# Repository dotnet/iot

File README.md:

# .NET IoT Libraries

.NET can be used to build applications for [IoT](https://en.wikipedia.org/wiki/Internet_of_things) devices and scenarios. IoT applications typically interact with sensors, displays and input devices that require the use of [GPIO pins](https://en.wikipedia.org/wiki/General-purpose_input/output), serial ports or similar hardware.

> [!IMPORTANT]
> This is the GitHub repo for the libraries. You might want to start with our [official documentation](https://docs.microsoft.com/dotnet/iot/).

This repository contains the [System.Device.Gpio](https://www.nuget.org/packages/System.Device.Gpio) library and implementations for various boards like [Raspberry Pi](https://www.raspberrypi.org/) and [Hummingboard](https://www.solid-run.com/nxp-family/hummingboard/).

The repository also contains [Iot.Device.Bindings](https://www.nuget.org/packages/Iot.Device.Bindings), a growing set of community-maintained [device bindings](src/devices/README.md) for IoT components.

The libraries in this repository are community-maintained and do not have a formal support commitment. Existing versions are not serviced. Fixes may be included in a future minor or major release.

> [!NOTE]
> This repository is still in experimental stage and all APIs are subject to changes.

## Hardware requirements

While most of the bindings and examples in this project require and are designed to support specific hardware (such as [LCD displays](src/devices/CharacterLcd), [temperature sensors](src/devices/Dhtxx), [single-board computers](src/devices/Board/RaspberryPiBoard.cs), [microcontrollers](src/devices/Arduino), etc.), the library itself tries to be as hardware-independent as possible. Some bindings are even written to showcase the use of IOT interfaces with hardware that is already present in normal desktop computers (such as [keyboards](src/devices/Board/KeyboardGpioDriver.cs) or [CPU temperature sensors](src/devices/HardwareMonitor)). So to get started, you do not need expensive hardware. Or you can start out with cheap stuff, such as an Arduino Uno.

## .NET Versions

Both libraries in this repository are cross-targeting .NET Standard 2.0, .NET Core 3.1, and .NET 6.0. They can be used from any project targeting .NET Core 2.0 or higher, and also from .NET Framework or mono. If you are looking at a Micro Controller Unit (MCU) support, check [.NET nanoFramework](https://github.com/nanoframework/).

The sample projects target the latest stable .NET Version. This applies to the sample projects with each device as well as the example projects on the `/samples` directory.

## How to Install

From Visual Studio, you can just add a nuget by searching for `System.Device.Gpio` and `Iot.Device.Bindings`.

### Nightly Builds

You can also install the latest nightly builds of the .NET `System.Device.Gpio`, `Iot.Device.Bindings`, and `Iot.Device.Bindings.SkiaSharpAdapter` NuGet packages. These are automatically published from the latest commits to the main branch.

#### Azure DevOps Feed (No Authentication Required)

Add the nightly feed to your project:

```shell
# Add the Azure DevOps nightly feed (no authentication required)
dotnet nuget add source --name dotnet-iot-nightly "https://pkgs.dev.azure.com/dotnet/IoT/_packaging/nightly_iot_builds/nuget/v3/index.json"

# Install packages
dotnet add package System.Device.Gpio --source dotnet-iot-nightly --prerelease
dotnet add package Iot.Device.Bindings --source dotnet-iot-nightly --prerelease
dotnet add package Iot.Device.Bindings.SkiaSharpAdapter --source dotnet-iot-nightly --prerelease
```

Or add to your `NuGet.config`:

```xml
<packageSources>
  <add key="dotnet-iot-nightly" value="https://pkgs.dev.azure.com/dotnet/IoT/_packaging/nightly_iot_builds/nuget/v3/index.json" />
</packageSources>
```

### Official Build Status

## Contributing

For information on how to build this repository and to add new device bindings, please head out to [Contributing](Documentation/CONTRIBUTING.md).

Please contribute. We are primarily interested in the following:

* Improving quality and capability of the drivers for supported boards.
* Implementations for additional boards.
* [.NET device bindings](src/devices) for a wide variety of sensors, chips, displays and other components.
* Request a device binding or protocol that you need for your project ([file an issue](https://github.com/dotnet/iot/issues)).
* Links to blog posts or tweets that showcase .NET Core being used for great IoT scenarios ([file an issue](https://github.com/dotnet/iot/issues)).

## Getting Started

After installing, please see the following areas to learn more:

* [Official Documentation](https://docs.microsoft.com/dotnet/iot/) - Concepts, quickstarts, tutorials, and API reference documentation.
* [API Documentation](https://docs.microsoft.com/dotnet/api/?view=iot-dotnet-1.5) - Direct link to API reference documentation for all public interfaces. Be sure to choose the library version you are using.
* [Microsoft Learn interactive learning module](https://docs.microsoft.com/learn/modules/create-iot-device-dotnet/)
* [Let's Learn .NET: IoT livestream (September 2021)](https://www.youtube.com/watch?v=sKaSBh1M4M4)
* [.NET IoT 101 (Jan 2020)](https://channel9.msdn.com/Series/IoT-101) - An introduction series on how to create .NET IoT applications with a Raspberry Pi.
* [Hardware Documentation](Documentation/README.md) - Resources related to electronics, devices, vendors, software and other IoT topics.
* [Samples](samples/README.md) - Step-by-step instructions on building your first app.
* [Roadmap](Documentation/roadmap.md) - Areas planned or currently being worked on.

All bindings (src/devices) contains a `samples` folder where you will find examples on how to use each of the devices, sensor, displays and other components.

**Important**: Please make sure you are using tag that correspond to your package version to browse and reuse the samples' code.

Once you have selected the right branch, you can browse the repository. The main branch contains code that is always the latest and may not been yet released to a package. So if you are using the 1.2 package, please select 1.2 tag before browsing the source code.

### Tutorials

* [Web service using SenseHat by Dawid Borycki (Aug 2019)](https://msdn.microsoft.com/magazine/mt833493)

## Community

This project has adopted the code of conduct defined by the [Contributor Covenant](https://contributor-covenant.org/)
to clarify expected behavior in our community. For more information, see the [.NET Foundation Code of Conduct](https://dotnetfoundation.org/code-of-conduct).

## License

.NET (including the iot repo) is licensed under the [MIT license](LICENSE).

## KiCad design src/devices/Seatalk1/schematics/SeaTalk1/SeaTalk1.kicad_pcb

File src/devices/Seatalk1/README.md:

# Seatalk 1 Interface

## Summary

Seatalk, also called Seatalk1, is a bus protocol used by the marine equipment company Raymarine. It is used as a protocol to connect various devices on a boat, such as depth sounders, anemometers (wind sensors), autopilots and displays. The protocol is the successor of NMEA-0183, providing the main benefit of being able to connect various devices to a single bus, without the need of complex star networks and bridges as it was required for NMEA-0183.

Data transfer uses a slow transmission rate of 4800 Baud, but this makes the bus quite stable with respect to interference. Collisions do occur, but as most messages are repeated at least every second, lost messages are typically negligible.

Seatalk has been superseeded by NMEA-2000, but some older devices are still only available with NMEA-0183 or Seatalk. Interfaces to convert between the various standards are available from different vendors.

> Note: Seatalk is often called Seatalk1, to distinguish it from SeatalkNG (Seatalk "Next Generation"). The latter is a branded version of NMEA-2000. NMEA-2000 and SeatalkNG are binary and electrically compatible, but use different plugs and sockets.

## Binding Notes

The binding provides the message definitions for various Seatalk messages. Using the proper interface (see below), it supports receiving and transmitting Seatalk messages. The binding is primarily intended to control older autopilots, such as the Raymarine ST1000+ and ST2000+. Not all known sentence types are supported, but the binding allows registering of further messages.

A bi-directional Seatalk to NMEA-0183 message converter is also included.

Example: (for full source, see example directory)

```csharp
_seatalk = new SeatalkInterface("/dev/ttyAMA2"); // Or some other serial interface
_seatalk.MessageReceived += ParserOnNewMessageDecoded;
_seatalk.StartDecode();
var ctrl = _seatalk.GetAutopilotRemoteController();

if (ctrl.SetStatus(AutopilotStatus.Auto, ref directionConfirmation))
{
    Console.WriteLine("Autopilot set to AUTO mode");
}
else
{
    Console.WriteLine("Setting AUTO mode FAILED!");
}

await Task.Delay(500);

NavigationToWaypoint wp = new NavigationToWaypoint()
{
    BearingToDestination = Angle.FromDegrees(10),
    CrossTrackError = Length.FromNauticalMiles(-0.11),
    DistanceToDestination = Length.FromNauticalMiles(51.3),
};

_seatalk.SendMessage(wp);

private void ParserOnNewMessageDecoded(SeatalkMessage obj)
{
    if (obj is Keystroke keystroke)
    {
        Console.WriteLine();
        Console.WriteLine($"Pressed key(s): {keystroke}");
    }
}

```

## Physical interface

The physical bus uses a kind of UART protocol, but since it uses a single wire both for sending and receiving, additional electronics are required to connect the bus to an UART (RS-232) interface. Protocol converters are available on the market. The following scheme shows a schematic that allows connecting a Seatalk network to a Raspberry Pi. The seatalk cable is connected to J3. The grey wire from the bus goes to GND, the yellow wire is the data wire and the red wire is +12V. In this schematic, connecting the 12V wire is optional as long as there's at least one other device on the bus that provides the necessary pull-up. The wiring shows a connection to TXD2/RXD2 (ttyAMA2 on linux), as this interface is easier to configure than the default one on GPIO14/15, as long as it's enabled in `boot/config.txt` with `dtoverlay=uart2`.

When connecting to a default RS-232 interface (e.g. using an USB-to-RS-232 converter), the inverting stages Q2 on RXD and Q5 on TXD should be skipped. Powering the entire wiring via 12V should work with some minor adjustments, such as changing R9 to 470Ω to avoid destroying D1.

## References

Many tanks to Thomas Knauf for his extensive Seatalk protocol analysis. See [here](http://www.thomasknauf.de/seatalk.htm)

OpenCPN Seatalk Support [here](https://opencpn.org/wiki/dokuwiki/doku.php?id=opencpn:supplementary_software:seatalk).

The OpenCPN plugin "Raymarine Autopilot" can send the required keypress sentences for remote-controlling an autopilot, but needs an NMEA-0183 to Seatalk1 bridge, which can be built using this binding.

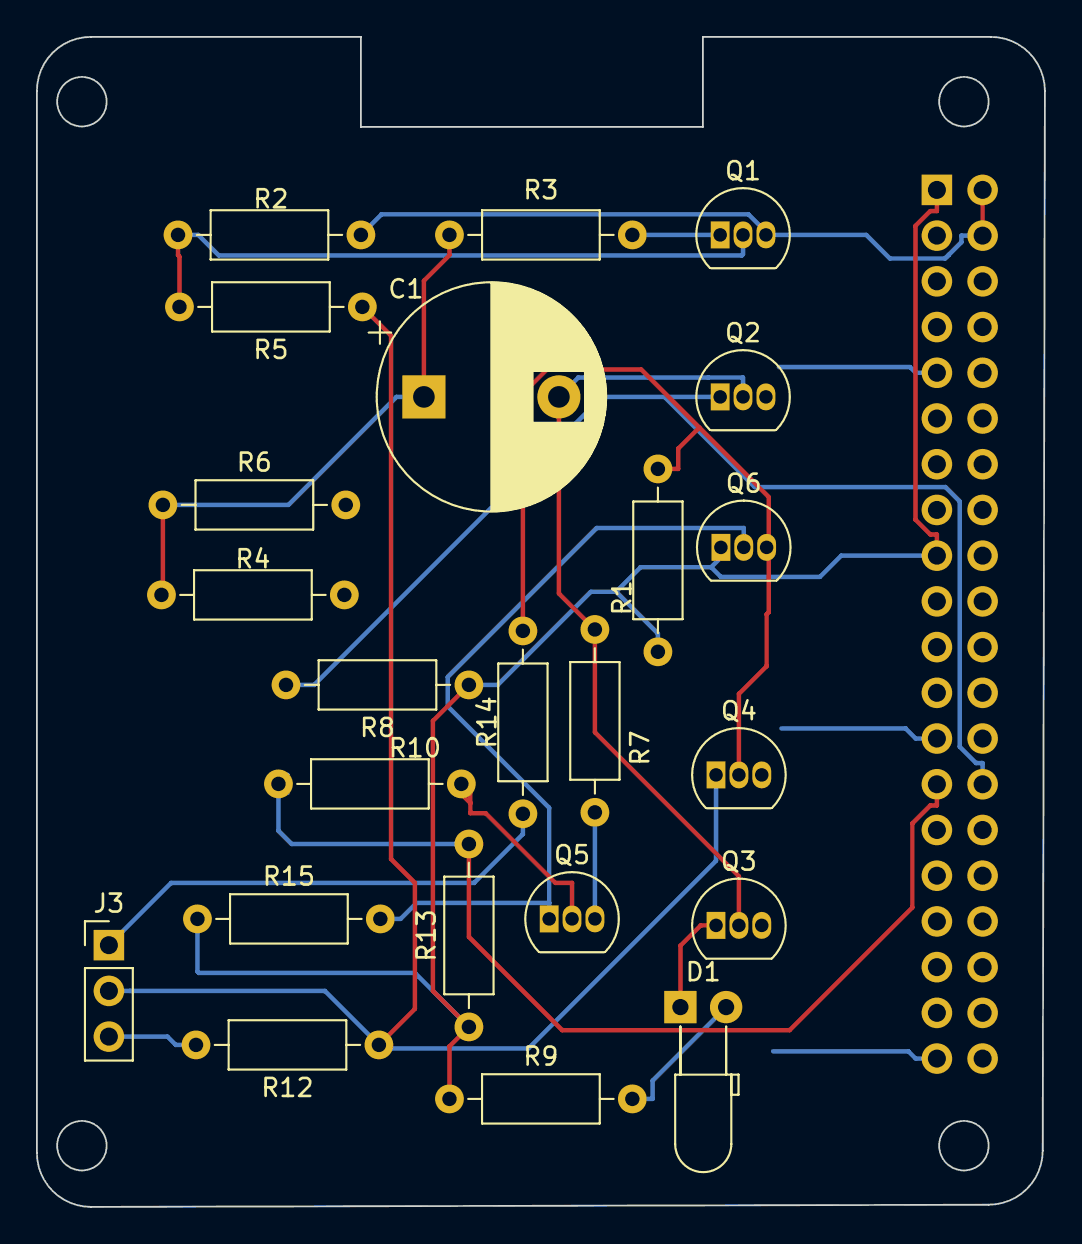
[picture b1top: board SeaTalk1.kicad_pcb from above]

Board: 2 copper layers, 56.0 x 65.0 mm, 24 parts (1 on the bottom side), 16 nets.

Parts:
C1: 150u; CP_Radial_D12.5mm_P7.50mm
D1: blue; LED_D3.0mm_Horizontal_O3.81mm_Z6.0mm
J1: Raspberry_Pi_2_3; PinSocket_2x20_P2.54mm_Vertical
J3: Conn_01x03_Pin; PinHeader_1x03_P2.54mm_Vertical
Q1: BC557; TO-92_Inline
Q2, Q3, Q4, Q5, Q6: BC547; TO-92_Inline
R1, R7: 22k; R_Axial_DIN0207_L6.3mm_D2.5mm_P10.16mm_Horizontal
R2, R3, R8, R14: 2.2k; R_Axial_DIN0207_L6.3mm_D2.5mm_P10.16mm_Horizontal
R4, R5, R6: 4.7k; R_Axial_DIN0207_L6.3mm_D2.5mm_P10.16mm_Horizontal
R9: 100; R_Axial_DIN0207_L6.3mm_D2.5mm_P10.16mm_Horizontal
R10: 1.5k; R_Axial_DIN0207_L6.3mm_D2.5mm_P10.16mm_Horizontal
R12, R13, R15: 10k; R_Axial_DIN0207_L6.3mm_D2.5mm_P10.16mm_Horizontal

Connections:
GND: J1.6 (GND), J1.9 (GND), J1.14 (GND), J1.20 (GND), J1.25 (GND), J1.30 (GND), J1.34 (GND), J1.39 (GND), J3.1, Q2.3 (E), Q3.3 (E), Q4.3 (E), Q5.3 (E), R4.2, R6.2, R7.2, R14.2
unnamed: C1.1, R3.2, R4.1, R6.1
unnamed: D1.2 (A), R9.2
unnamed: D1.1 (K), Q3.1 (C)
unnamed: J1.28 (ID_SC/GPIO1), Q2.1 (C), R8.2
unnamed: J3.3, R12.2
unnamed: Q1.2 (B), R2.2, R5.2
unnamed: Q1.1 (C), R3.1
unnamed: C1.2, Q2.2 (B), Q3.2 (B), R7.1
unnamed: Q4.2 (B), Q6.3 (E), R1.2, R14.1
unnamed: Q5.2 (B), R10.2
unnamed: Q5.1 (C), Q6.2 (B), R15.2
SEATALK: J3.2, Q4.1 (C), R5.1, R12.1
TXD: J1.27 (ID_SD/GPIO0), R10.1, R13.2
VCC_3.3: J1.1 (3V3), J1.17 (3V3), Q6.1 (C), R1.1, R8.1, R9.1, R13.1, R15.1
VCC_5.0: J1.2 (5V), J1.4 (5V), Q1.3 (E), R2.1

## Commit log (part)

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2026-05-09 Looks better now, maybe?
2026-05-10 Bump Microsoft.DotNet.Helix.Sdk from 9.0.0-beta.26223.2 to 9.0.0-beta.26255.11 (#2523)
    ---
    updated-dependencies:
    - dependency-name: Microsoft.DotNet.Helix.Sdk
    dependency-version: 9.0.0-beta.26255.11
    dependency-type: direct:production
    update-type: version-update:semver-patch
2026-05-11 Designed new filter interface
2026-05-13 Bump Microsoft.DotNet.GenAPI from 9.0.0-beta.26255.11 to 9.0.0-beta.26261.1
    ---
    updated-dependencies:
    - dependency-name: Microsoft.DotNet.GenAPI
    dependency-version: 9.0.0-beta.26261.1
    dependency-type: direct:production
    update-type: version-update:semver-patch
2026-05-13 Bump Microsoft.Extensions.Logging from 10.0.7 to 10.0.8
    ---
    updated-dependencies:
    - dependency-name: Microsoft.Extensions.Logging
    dependency-version: 10.0.8
    dependency-type: direct:production
    update-type: version-update:semver-patch
2026-05-13 Bump System.Drawing.Common from 10.0.7 to 10.0.8
    ---
    updated-dependencies:
    - dependency-name: System.Drawing.Common
    dependency-version: 10.0.8
    dependency-type: direct:production
    update-type: version-update:semver-patch
2026-05-13 Bump Microsoft.Extensions.Logging.Abstractions from 10.0.7 to 10.0.8
    ---
    updated-dependencies:
    - dependency-name: Microsoft.Extensions.Logging.Abstractions
    dependency-version: 10.0.8
    dependency-type: direct:production
    update-type: version-update:semver-patch
2026-05-13 Bump System.IO.Ports from 10.0.7 to 10.0.8
    ---
    updated-dependencies:
    - dependency-name: System.IO.Ports
    dependency-version: 10.0.8
    dependency-type: direct:production
    update-type: version-update:semver-patch
2026-05-13 Bump System.Management from 10.0.7 to 10.0.8
    ---
    updated-dependencies:
    - dependency-name: System.Management
    dependency-version: 10.0.8
    dependency-type: direct:production
    update-type: version-update:semver-patch
2026-05-14 Bump System.IO.Pipelines from 10.0.7 to 10.0.8 (#2532)
    ---
    updated-dependencies:
    - dependency-name: System.IO.Pipelines
    dependency-version: 10.0.8
    dependency-type: direct:production
    update-type: version-update:semver-patch
2026-05-14 Bump Microsoft.Extensions.Logging from 10.0.7 to 10.0.8 (#2530)
    ---
    updated-dependencies:
    - dependency-name: Microsoft.Extensions.Logging
    dependency-version: 10.0.8
    dependency-type: direct:production
    update-type: version-update:semver-patch
2026-05-14 Bump Microsoft.DotNet.Arcade.Sdk from 9.0.0-beta.26255.11 to 9.0.0-beta.26261.1 (#2527)
    ---
    updated-dependencies:
    - dependency-name: Microsoft.DotNet.Arcade.Sdk
    dependency-version: 9.0.0-beta.26261.1
    dependency-type: direct:production
    update-type: version-update:semver-patch
2026-05-14 Bump Microsoft.DotNet.Helix.Sdk from 9.0.0-beta.26255.11 to 9.0.0-beta.26261.1
    ---
    updated-dependencies:
    - dependency-name: Microsoft.DotNet.Helix.Sdk
    dependency-version: 9.0.0-beta.26261.1
    dependency-type: direct:production
    update-type: version-update:semver-patch
2026-05-14 Bump System.IO.Ports from 10.0.7 to 10.0.8 (#2534)
    ---
    updated-dependencies:
    - dependency-name: System.IO.Ports
    dependency-version: 10.0.8
    dependency-type: direct:production
    update-type: version-update:semver-patch
2026-05-14 Fix SpiAdapter.Read buffer length mismatch for TransferFullDuplex
    Allocate writeBuffer at the same length as readBuffer (buffer.Length + 2)
    with OpCode and register address in the first 2 bytes. This matches the
    pattern used in Mcp25xxx and fixes the ArgumentException thrown by
    UnixSpiDevice.TransferFullDuplex when buffers differ in length.
    Update the test mock's TransferFullDuplex to only forward the 2-byte
    command prefix (OpCode + RegisterAddress) to Write, since remaining
2026-05-14 Bump Microsoft.DotNet.Helix.Sdk from 9.0.0-beta.26255.11 to 9.0.0-beta.26261.1 (#2528)
    ---
    updated-dependencies:
    - dependency-name: Microsoft.DotNet.Helix.Sdk
    dependency-version: 9.0.0-beta.26261.1
    dependency-type: direct:production
    update-type: version-update:semver-patch
2026-05-18 Update dependencies from https://github.com/dotnet/arcade build 20260511.1 (#2538)
    On relative base path root
    Microsoft.DotNet.Arcade.Sdk , Microsoft.DotNet.GenAPI , Microsoft.DotNet.Helix.Sdk From Version 9.0.0-beta.25626.6 -> To Version 9.0.0-beta.26261.1
2026-05-20 Bump System.Drawing.Common from 10.0.7 to 10.0.8 (#2539)
    ---
    updated-dependencies:
    - dependency-name: System.Drawing.Common
    dependency-version: 10.0.8
    dependency-type: direct:production
    update-type: version-update:semver-patch
2026-05-21 AI review feedback
2026-05-27 Bump Microsoft.DotNet.Arcade.Sdk from 9.0.0-beta.26261.1 to 9.0.0-beta.26276.6
    ---
    updated-dependencies:
    - dependency-name: Microsoft.DotNet.Arcade.Sdk
    dependency-version: 9.0.0-beta.26276.6
    dependency-type: direct:production
    update-type: version-update:semver-patch
2026-05-27 Bump SkiaSharp from 3.119.2 to 3.119.4
    ---
    updated-dependencies:
    - dependency-name: SkiaSharp
    dependency-version: 3.119.4
    dependency-type: direct:production
    update-type: version-update:semver-patch
2026-05-27 Bump Microsoft.DotNet.GenAPI from 9.0.0-beta.26261.1 to 9.0.0-beta.26276.6 (#2545)
    ---
    updated-dependencies:
    - dependency-name: Microsoft.DotNet.GenAPI
    dependency-version: 9.0.0-beta.26276.6
    dependency-type: direct:production
    update-type: version-update:semver-patch
2026-05-27 Bump Microsoft.Extensions.Logging.Abstractions from 10.0.7 to 10.0.8 (#2546)
    ---
    updated-dependencies:
    - dependency-name: Microsoft.Extensions.Logging.Abstractions
    dependency-version: 10.0.8
    dependency-type: direct:production
    update-type: version-update:semver-patch
2026-05-27 Bump SkiaSharp.NativeAssets.Linux from 3.119.2 to 3.119.4
    ---
    updated-dependencies:
    - dependency-name: SkiaSharp.NativeAssets.Linux
    dependency-version: 3.119.4
    dependency-type: direct:production
    update-type: version-update:semver-patch
2026-05-27 Bump Microsoft.DotNet.Arcade.Sdk from 9.0.0-beta.26261.1 to 9.0.0-beta.26276.6 (#2543)
    ---
    updated-dependencies:
    - dependency-name: Microsoft.DotNet.Arcade.Sdk
    dependency-version: 9.0.0-beta.26276.6
    dependency-type: direct:production
    update-type: version-update:semver-patch
2026-05-27 Bump Microsoft.DotNet.Helix.Sdk from 9.0.0-beta.26261.1 to 9.0.0-beta.26276.6
    ---
    updated-dependencies:
    - dependency-name: Microsoft.DotNet.Helix.Sdk
    dependency-version: 9.0.0-beta.26276.6
    dependency-type: direct:production
    update-type: version-update:semver-patch
2026-05-28 Start eventually using the new filter type
2026-05-28 Bump Microsoft.DotNet.Helix.Sdk from 9.0.0-beta.26261.1 to 9.0.0-beta.26276.6 (#2544)
    ---
    updated-dependencies:
    - dependency-name: Microsoft.DotNet.Helix.Sdk
    dependency-version: 9.0.0-beta.26276.6
    dependency-type: direct:production
    update-type: version-update:semver-patch
2026-05-28 Fix unhandled OverflowException in NMEA parser for malformed sentences
2026-06-01 Update dependencies from https://github.com/dotnet/arcade build 20260528.4 (#2550)
    On relative base path root
    Microsoft.DotNet.Arcade.Sdk , Microsoft.DotNet.GenAPI , Microsoft.DotNet.Helix.Sdk From Version 9.0.0-beta.26261.1 -> To Version 9.0.0-beta.26278.4
2026-06-02 Fix NMEA parser intermittent crash on stream disposal
    Catch InvalidOperationException in the parser thread's ReadLine path.
    NetworkStream.Read throws InvalidOperationException ("The stream does
    not support reading") rather than ObjectDisposedException when the
    underlying stream has been disposed (CanRead == false). This happens
    during StopDecode while the parser thread is blocked inside ReadLine,
    causing an unhandled exception that crashed the test host.
2026-06-02 Update stale BuildHat firmware and read version/signature line-by-line
2026-06-02 Clarify MaximumLines rationale in PortReadUntil
2026-06-02 Add missing integral-limit param to Build HAT pid commands
2026-06-02 Allow configuring FT4222 I2C master clock frequency
2026-06-02 Simplify default expressions in CanRaw
2026-06-02 Address review: simplify PATH probing in ProcessSettingsFactory
2026-06-02 Fix stray closing brace breaking compilation in Ft4222I2cBus
2026-06-02 Fix SA1412 build failure: store ProcessSettingsFactoryTests.cs as UTF-8 with BOM
2026-06-04 Bump Microsoft.DotNet.Helix.Sdk from 9.0.0-beta.26278.4 to 9.0.0-beta.26301.4
    ---
    updated-dependencies:
    - dependency-name: Microsoft.DotNet.Helix.Sdk
    dependency-version: 9.0.0-beta.26301.4
    dependency-type: direct:production
    update-type: version-update:semver-patch
2026-06-04 Bump Microsoft.DotNet.Helix.Sdk from 9.0.0-beta.26278.4 to 9.0.0-beta.26301.4 (#2562)
    ---
    updated-dependencies:
    - dependency-name: Microsoft.DotNet.Helix.Sdk
    dependency-version: 9.0.0-beta.26301.4
    dependency-type: direct:production
    update-type: version-update:semver-patch
2026-06-04 Bump Microsoft.DotNet.Arcade.Sdk from 9.0.0-beta.26278.4 to 9.0.0-beta.26301.4
    ---
    updated-dependencies:
    - dependency-name: Microsoft.DotNet.Arcade.Sdk
    dependency-version: 9.0.0-beta.26301.4
    dependency-type: direct:production
    update-type: version-update:semver-patch
2026-06-04 Bump Microsoft.DotNet.Arcade.Sdk from 9.0.0-beta.26278.4 to 9.0.0-beta.26301.4 (#2560)
    ---
    updated-dependencies:
    - dependency-name: Microsoft.DotNet.Arcade.Sdk
    dependency-version: 9.0.0-beta.26301.4
    dependency-type: direct:production
    update-type: version-update:semver-patch
2026-06-06 Adjust Ft4222I2cBus API for review feedback
2026-06-06 Clarify Ft4222I2cBus constructor docs
2026-06-10 Bump Microsoft.Extensions.Logging from 10.0.8 to 10.0.9
    ---
    updated-dependencies:
    - dependency-name: Microsoft.Extensions.Logging
    dependency-version: 10.0.9
    dependency-type: direct:production
    update-type: version-update:semver-patch
2026-06-10 Bump System.Drawing.Common from 10.0.8 to 10.0.9
    ---
    updated-dependencies:
    - dependency-name: System.Drawing.Common
    dependency-version: 10.0.9
    dependency-type: direct:production
    update-type: version-update:semver-patch
2026-06-10 Bump Microsoft.Extensions.Logging.Abstractions from 10.0.8 to 10.0.9
    ---
    updated-dependencies:
    - dependency-name: Microsoft.Extensions.Logging.Abstractions
    dependency-version: 10.0.9
    dependency-type: direct:production
    update-type: version-update:semver-patch
2026-06-10 Bump System.IO.Ports from 10.0.8 to 10.0.9
    ---
    updated-dependencies:
    - dependency-name: System.IO.Ports
    dependency-version: 10.0.9
    dependency-type: direct:production
    update-type: version-update:semver-patch
2026-06-10 Bump System.Management from 10.0.8 to 10.0.9
    ---
    updated-dependencies:
    - dependency-name: System.Management
    dependency-version: 10.0.9
    dependency-type: direct:production
    update-type: version-update:semver-patch
2026-06-10 Bump System.Management from 10.0.8 to 10.0.9 (#2569)
    ---
    updated-dependencies:
    - dependency-name: System.Management
    dependency-version: 10.0.9
    dependency-type: direct:production
    update-type: version-update:semver-patch
2026-06-10 Bump System.IO.Ports from 10.0.8 to 10.0.9 (#2568)
    ---
    updated-dependencies:
    - dependency-name: System.IO.Ports
    dependency-version: 10.0.9
    dependency-type: direct:production
    update-type: version-update:semver-patch
2026-06-10 Bump System.IO.Pipelines from 10.0.8 to 10.0.9 (#2566)
    ---
    updated-dependencies:
    - dependency-name: System.IO.Pipelines
    dependency-version: 10.0.9
    dependency-type: direct:production
    update-type: version-update:semver-patch
2026-06-14 Add missing FT4222I2cBus XML doc
